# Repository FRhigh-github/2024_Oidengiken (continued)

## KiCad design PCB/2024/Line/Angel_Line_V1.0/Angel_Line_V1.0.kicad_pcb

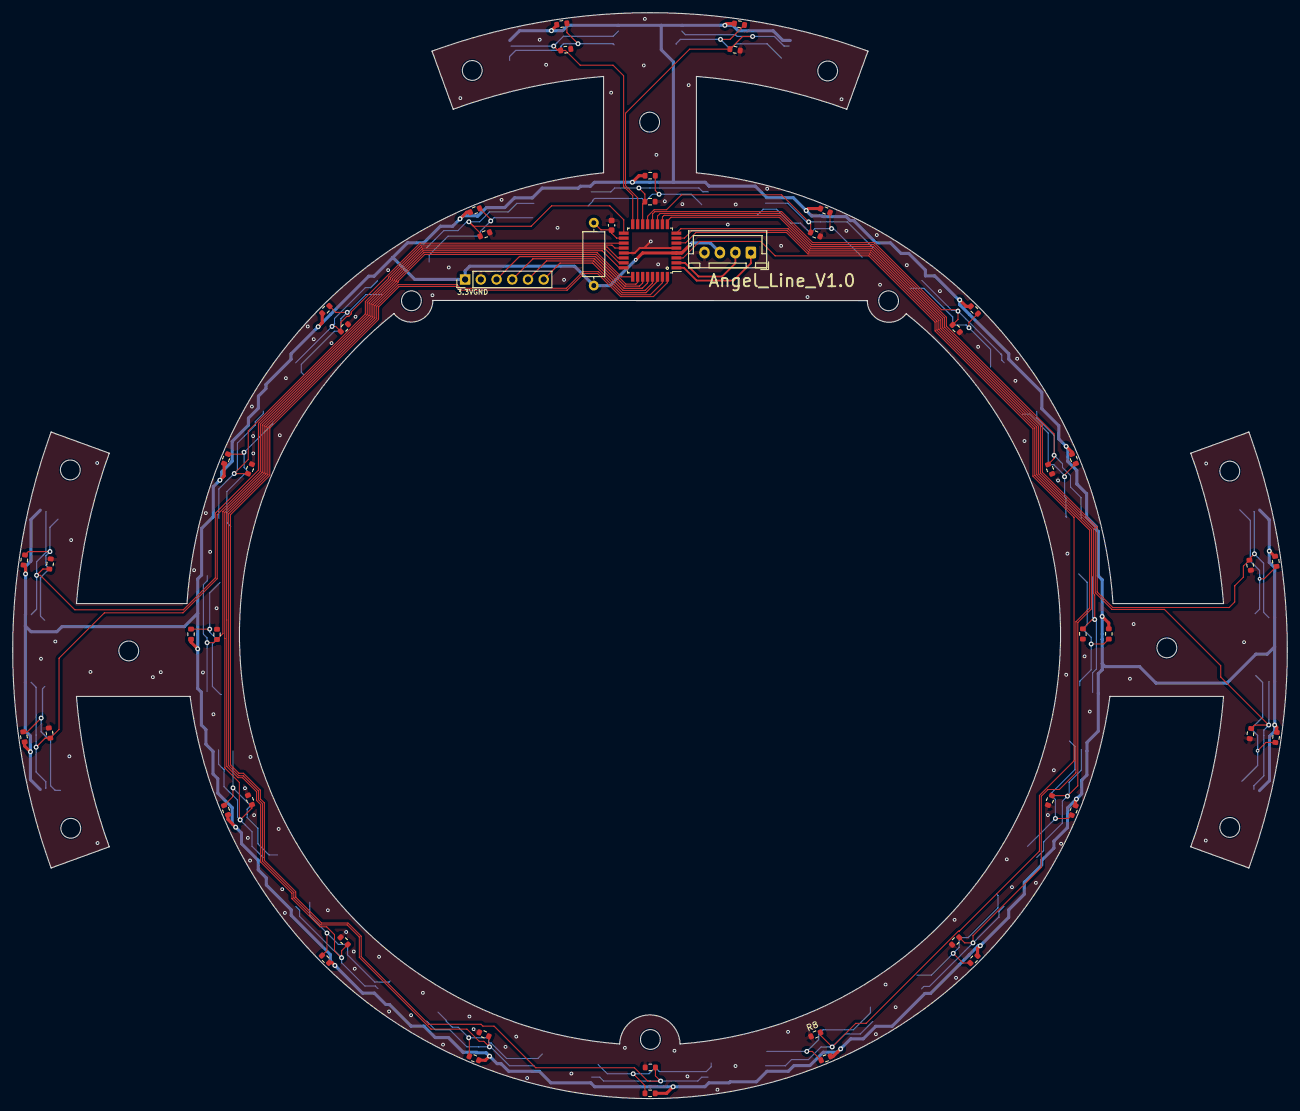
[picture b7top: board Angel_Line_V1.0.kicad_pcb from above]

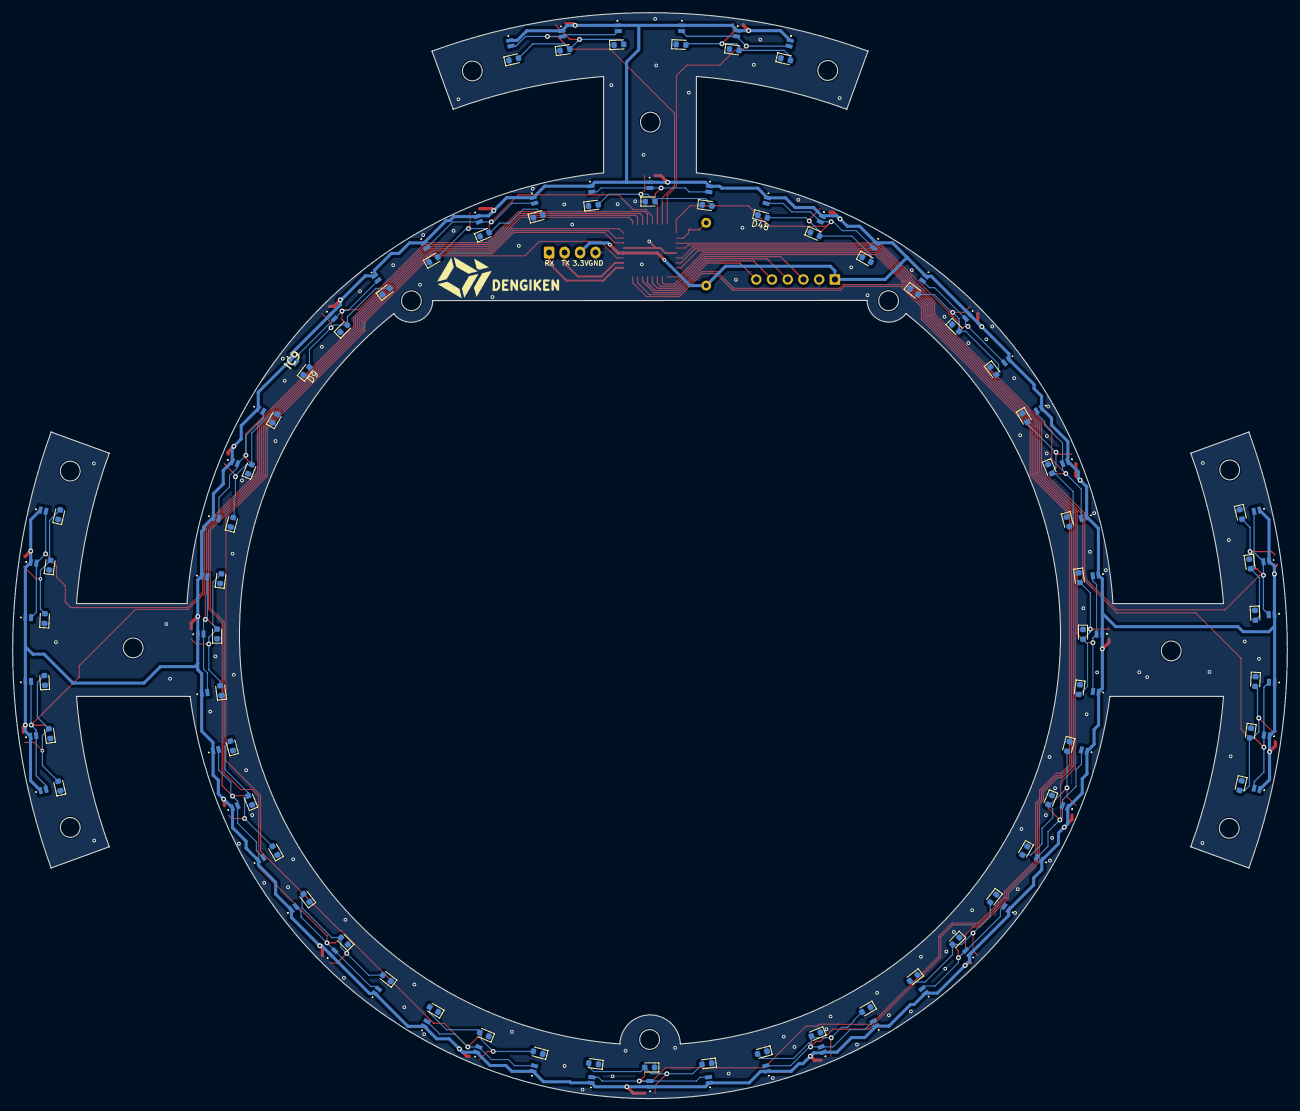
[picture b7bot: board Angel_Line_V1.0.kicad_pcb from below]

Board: 2 copper layers, 206.0 x 175.5 mm, 181 parts (132 on the bottom side), 53 nets.

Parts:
C1: C; C_0603_1608Metric
D1, D2, D3, D4, D5, D6, D7, D8, D9, D10, D11, D12, D13, D14, D15, D16, D17, D18, D19, D20, D21, D22, D23, D24, D25, D26, D27, D28, D29, D30, D31, D32, D33, D34, D35, D36, D37, D38, D39, D40, D41, D42, D43, D44, D45, D46, D47, D48, D49, D50, D51, D52, D53, D54, D55, D56, D57, D58, D59, D60, D61, D62, D63, D64, D65, D66: LED; LED_0603_1608Metric
IC1, IC2, IC3, IC4, IC5, IC6, IC7, IC8, IC9, IC10, IC11, IC12, IC13, IC14, IC15, IC16, IC17, IC18, IC19, IC20, IC21, IC22, IC23, IC24, IC25, IC26, IC27, IC28, IC29, IC30, IC31, IC32, IC33, IC34, IC35, IC36, IC37, IC38, IC39, IC40, IC41, IC42, IC43, IC44, IC45, IC46, IC47, IC48, IC49, IC50, IC51, IC52, IC53, IC54, IC55, IC56, IC57, IC58, IC59, IC60, IC67, IC68, IC69, IC70, IC71, IC72: NJL7502R
J1: Conn_01x06_Female; PinHeader_1x06_P2.54mm_Vertical
J2: Conn_01x04_Socket; JST_XH_B4B-XH-A_1x04_P2.50mm_Vertical
L1: L; L_Axial_L7.0mm_D3.3mm_P10.16mm_Horizontal_Fastron_MICC
R1, R2, R3, R4, R5, R6, R7, R8, R9, R10, R11, R12, R13, R14, R15, R16, R21, R22, R23, R24, R27, R28: 50k; R_0603_1608Metric
R17, R18, R19, R20, R25, R26, R29, R30, R31, R32, R33, R34, R35, R36, R37, R38, R39, R40, R41, R42, R43, R44: 100; R_0603_1608Metric
U1: ATtiny828-A; TQFP-32_7x7mm_P0.8mm

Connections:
A0: IC1.2 (E), IC2.2 (E), IC3.2 (E), R1.2, U1.14 (PA5)
A1: IC4.2 (E), IC5.2 (E), IC6.2 (E), R2.2, U1.13 (PA4)
A2: IC7.2 (E), IC8.2 (E), IC9.2 (E), R3.2, U1.12 (PA3)
A3: IC10.2 (E), IC11.2 (E), IC12.2 (E), R4.2, U1.11 (PA2)
A4: IC13.2 (E), IC14.2 (E), IC15.2 (E), R5.2, U1.8 (PC7)
A5: IC16.2 (E), IC17.2 (E), IC18.2 (E), R6.2, U1.7 (PC6)
A6: IC19.2 (E), IC20.2 (E), IC21.2 (E), R7.2, U1.6 (PC5)
A7: IC22.2 (E), IC23.2 (E), IC24.2 (E), R8.2, U1.3 (PC4)
A8: IC25.2 (E), IC26.2 (E), IC27.2 (E), R9.2, U1.32 (PC1)
A9: IC28.2 (E), IC29.2 (E), IC30.2 (E), R10.2, U1.31 (PC0)
A10: IC31.2 (E), IC32.2 (E), IC33.2 (E), R11.2, U1.26 (PB7)
A11: IC34.2 (E), IC35.2 (E), IC36.2 (E), R12.2, U1.25 (PB6)
A12: IC37.2 (E), IC38.2 (E), IC39.2 (E), R13.2, U1.24 (PB5)
A13: IC40.2 (E), IC41.2 (E), IC42.2 (E), R14.2, U1.20 (PB2)
A14: IC43.2 (E), IC44.2 (E), IC45.2 (E), R15.2, U1.19 (PB1)
A15: IC46.2 (E), IC47.2 (E), IC48.2 (E), R16.2, U1.17 (PB0)
A16: IC67.2 (E), IC68.2 (E), IC69.2 (E), R27.2, U1.16 (PA7)
A17: IC70.2 (E), IC71.2 (E), IC72.2 (E), R28.2, U1.15 (PA6)
A18: IC49.2 (E), IC50.2 (E), IC51.2 (E), R21.2, U1.10 (PA1)
A19: IC52.2 (E), IC53.2 (E), IC54.2 (E), R22.2, U1.9 (PA0)
A20: IC55.2 (E), IC56.2 (E), IC57.2 (E), R23.2, U1.23 (PB4)
A21: IC58.2 (E), IC59.2 (E), IC60.2 (E), R24.2, U1.22 (PB3)
Angel_RX: J2.1, U1.1 (PC2)
Angel_TX: J2.2, U1.2 (PC3)
MISO: J1.4, U1.28 (PD1)
MOSI: J1.3, U1.27 (PD0)
unnamed: D1.2 (A), D2.2 (A), D3.2 (A), R17.2
unnamed: D4.2 (A), D5.2 (A), D6.2 (A), R18.2
unnamed: D7.2 (A), D8.2 (A), D9.2 (A), R19.2
unnamed: D10.2 (A), D11.2 (A), D12.2 (A), R20.2
unnamed: D13.2 (A), D14.2 (A), D15.2 (A), R25.2
unnamed: D16.2 (A), D17.2 (A), D18.2 (A), R26.2
unnamed: D19.2 (A), D20.2 (A), D21.2 (A), R29.2
unnamed: D22.2 (A), D23.2 (A), D24.2 (A), R30.2
unnamed: D25.2 (A), D26.2 (A), D27.2 (A), R31.2
unnamed: D28.2 (A), D29.2 (A), D30.2 (A), R32.2
unnamed: D31.2 (A), D32.2 (A), D33.2 (A), R33.2
unnamed: D34.2 (A), D35.2 (A), D36.2 (A), R34.2
unnamed: D37.2 (A), D38.2 (A), D39.2 (A), R35.2
unnamed: D40.2 (A), D41.2 (A), D42.2 (A), R36.2
unnamed: D43.2 (A), D44.2 (A), D45.2 (A), R37.2
unnamed: D46.2 (A), D47.2 (A), D48.2 (A), R38.2
unnamed: D49.2 (A), D50.2 (A), D51.2 (A), R39.2
unnamed: D52.2 (A), D53.2 (A), D54.2 (A), R40.2
unnamed: D55.2 (A), D56.2 (A), D57.2 (A), R41.2
unnamed: D58.2 (A), D59.2 (A), D60.2 (A), R42.2
unnamed: D61.2 (A), D62.2 (A), D63.2 (A), R43.2
unnamed: D64.2 (A), D65.2 (A), D66.2 (A), R44.2
RESET: J1.5, U1.29 (PD2/~RESET)
SCL: J1.6, U1.30 (PD3)
VCC: IC1.1 (C), IC2.1 (C), IC3.1 (C), IC4.1 (C), IC5.1 (C), IC6.1 (C), IC7.1 (C), IC8.1 (C), IC9.1 (C), IC10.1 (C), IC11.1 (C), IC12.1 (C), IC13.1 (C), IC14.1 (C), IC15.1 (C), IC16.1 (C), IC17.1 (C), IC18.1 (C), IC19.1 (C), IC20.1 (C), IC21.1 (C), IC22.1 (C), IC23.1 (C), IC24.1 (C), IC25.1 (C), IC26.1 (C), IC27.1 (C), IC28.1 (C), IC29.1 (C), IC30.1 (C), IC31.1 (C), IC32.1 (C), IC33.1 (C), IC34.1 (C), IC35.1 (C), IC36.1 (C), IC37.1 (C), IC38.1 (C), IC39.1 (C), IC40.1 (C), IC41.1 (C), IC42.1 (C), IC43.1 (C), IC44.1 (C), IC45.1 (C), IC46.1 (C), IC47.1 (C), IC48.1 (C), IC49.1 (C), IC50.1 (C), IC51.1 (C), IC52.1 (C), IC53.1 (C), IC54.1 (C), IC55.1 (C), IC56.1 (C), IC57.1 (C), IC58.1 (C), IC59.1 (C), IC60.1 (C), IC67.1 (C), IC68.1 (C), IC69.1 (C), IC70.1 (C), IC71.1 (C), IC72.1 (C), J1.1, J2.3, L1.1, R17.1, R18.1, R19.1, R20.1, R25.1, R26.1, R29.1, R30.1, R31.1, R32.1, R33.1, R34.1, R35.1, R36.1, R37.1, R38.1, R39.1, R40.1, R41.1, R42.1, R43.1, R44.1, U1.4 (VCC)
VCCA: C1.1, L1.2, U1.18 (AVCC)
VSS: C1.2, D1.1 (K), D2.1 (K), D3.1 (K), D4.1 (K), D5.1 (K), D6.1 (K), D7.1 (K), D8.1 (K), D9.1 (K), D10.1 (K), D11.1 (K), D12.1 (K), D13.1 (K), D14.1 (K), D15.1 (K), D16.1 (K), D17.1 (K), D18.1 (K), D19.1 (K), D20.1 (K), D21.1 (K), D22.1 (K), D23.1 (K), D24.1 (K), D25.1 (K), D26.1 (K), D27.1 (K), D28.1 (K), D29.1 (K), D30.1 (K), D31.1 (K), D32.1 (K), D33.1 (K), D34.1 (K), D35.1 (K), D36.1 (K), D37.1 (K), D38.1 (K), D39.1 (K), D40.1 (K), D41.1 (K), D42.1 (K), D43.1 (K), D44.1 (K), D45.1 (K), D46.1 (K), D47.1 (K), D48.1 (K), D49.1 (K), D50.1 (K), D51.1 (K), D52.1 (K), D53.1 (K), D54.1 (K), D55.1 (K), D56.1 (K), D57.1 (K), D58.1 (K), D59.1 (K), D60.1 (K), D61.1 (K), D62.1 (K), D63.1 (K), D64.1 (K), D65.1 (K), D66.1 (K), J1.2, J2.4, R1.1, R2.1, R3.1, R4.1, R5.1, R6.1, R7.1, R8.1, R9.1, R10.1, R11.1, R12.1, R13.1, R14.1, R15.1, R16.1, R21.1, R22.1, R23.1, R24.1, R27.1, R28.1, U1.5 (GND), U1.21 (GND)

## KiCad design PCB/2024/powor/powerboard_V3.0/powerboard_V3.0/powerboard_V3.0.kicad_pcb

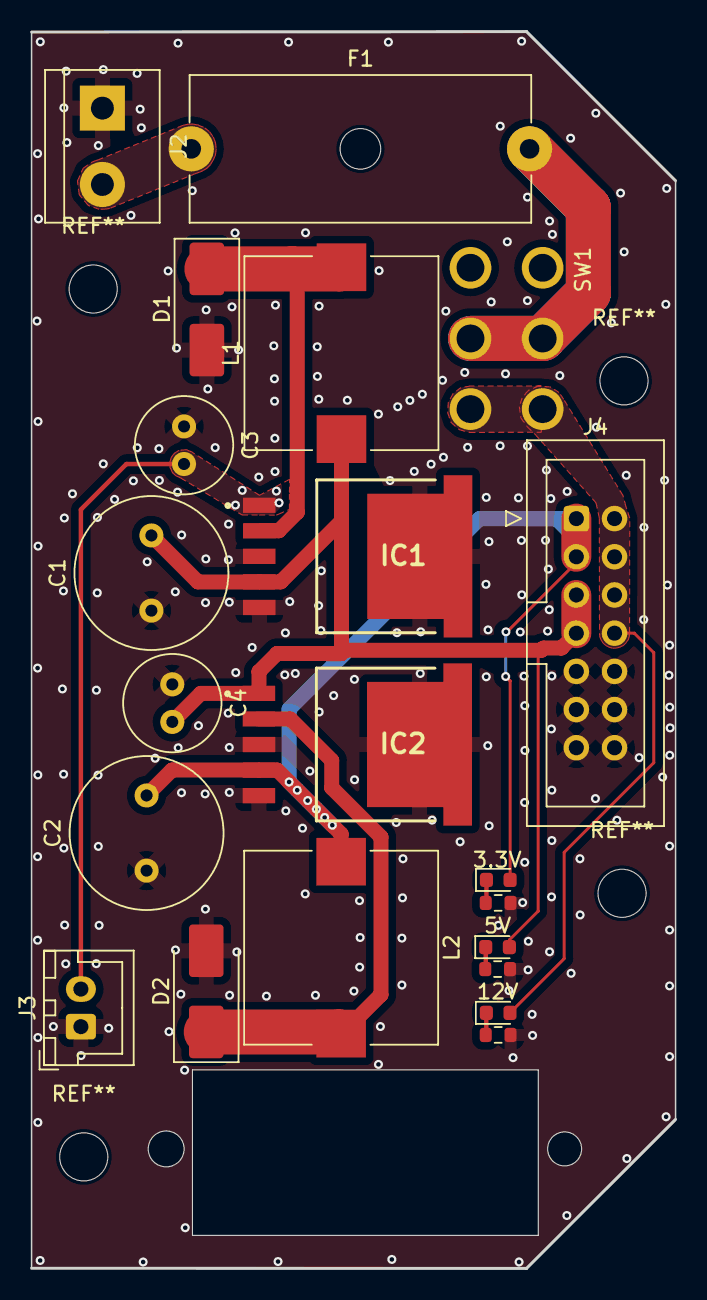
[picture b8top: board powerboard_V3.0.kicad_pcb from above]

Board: 2 copper layers, 42.8 x 82.3 mm, 21 parts (0 on the bottom side), 11 nets.

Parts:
3.3V, 5V, 12V: LED; LED_0603_1608Metric
C1, C2: 1000uF; C_Radial_D10.0mm_H12.5mm_P5.00mm
C3, C4: 100uF; C_Radial_D6.3mm_H7.0mm_P2.50mm
D1, D2: D; D_SMB_Handsoldering
F1: Fuse; Fuseholder_Cylinder-5x20mm_Schurter_0031_8201_Horizontal_Op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
IC1: LM2576SX-5.0_NOPB; KTT0005B
IC2: LM2576SX-3.3_NOPB; KTT0005B
J2: Conn_01x02_Female; TerminalBlock_bornier-2_P5.08mm
J3: 電圧計; JST_XH_B2B-XH-A_1x02_P2.50mm_Vertical
J4: Conn_02x07_Odd_Even; IDC-Header_2x07_P2.54mm_Vertical
L1, L2: 100uH; L_Vishay_IHLP-5050
R1, R2, R3: R; R_0603_1608Metric
SW1: SW_Push_DPDT; Toggle

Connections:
+3.3V: 3.3V.2 (A), C2.2, IC2.4 (FEEDBACK), J4.1, J4.3, L2.1
+5V: 5V.2 (A), C1.2, C4.2, IC1.4 (FEEDBACK), IC2.1 (VIN), J4.5, J4.7, L1.1
+12V: 12V.2 (A), C3.2, IC1.1 (VIN), J3.2, J4.2, J4.4, J4.6, J4.8, SW1.1 (A), SW1.4 (A)
GND: C1.1, C2.1, C3.1, C4.1, D1.2 (A), D2.2 (A), IC1.3 (GROUND), IC1.5 (~ON/OFF), IC1.6 (GND), IC2.3 (GROUND), IC2.5 (~ON/OFF), IC2.6 (GND), J2.1, J3.1, J4.9, J4.10, J4.11, J4.12, J4.13, J4.14, R1.1, R2.1, R3.1
unnamed: D1.1 (K), IC1.2 (OUTPUT), L1.2
unnamed: D2.1 (K), IC2.2 (OUTPUT), L2.2
unnamed: 5V.1 (K), R1.2
unnamed: 3.3V.1 (K), R2.2
unnamed: 12V.1 (K), R3.2
unnamed: F1.2, SW1.2 (B), SW1.5 (B)
unnamed: F1.1, J2.2

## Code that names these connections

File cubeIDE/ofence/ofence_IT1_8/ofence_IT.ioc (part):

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Mcu.Name=STM32F446R(C-E)Tx
Mcu.Package=LQFP64
Mcu.UserName=STM32F446RETx
PA0-WKUP.Mode=Asynchronous
PA0-WKUP.Signal=UART4_TX
PA1.Mode=Asynchronous
PA1.Signal=UART4_RX
PA10.Mode=Asynchronous
PA10.Signal=USART1_RX
PA13.GPIOParameters=GPIO_Label
PA13.GPIO_Label=TMS
PA13.Mode=Serial_Wire
PA13.Signal=SYS_JTMS-SWDIO
PA14.GPIOParameters=GPIO_Label
PA14.GPIO_Label=TCK
PA14.Mode=Serial_Wire
PA14.Signal=SYS_JTCK-SWCLK
PA2.GPIOParameters=GPIO_Label
PA2.GPIO_Label=USART_TX
PA2.Mode=Asynchronous
PA2.Signal=USART2_TX
PA3.GPIOParameters=GPIO_Label
PA3.GPIO_Label=USART_RX
PA3.Mode=Asynchronous
PA3.Signal=USART2_RX
PA5.GPIOParameters=GPIO_Label
PA5.GPIO_Label=LD2 [Green Led]
PA5.Signal=GPIO_Output
PA9.Mode=Asynchronous
PA9.Signal=USART1_TX
PB0.Signal=S_TIM3_CH3
PB1.Signal=S_TIM3_CH4
PB10.Signal=S_TIM2_CH3
PB2.Signal=S_TIM2_CH4
PB3.GPIOParameters=GPIO_Label
PB3.GPIO_Label=SWO
PB3.Signal=SYS_JTDO-SWO
PC0.GPIOParameters=GPIO_Label
PC0.GPIO_Label=ST_SW
PC0.Signal=GPXTI0
PC10.Mode=Asynchronous
PC10.Signal=USART3_TX
PC11.Mode=Asynchronous
PC11.Signal=USART3_RX
PC12.Mode=Asynchronous
PC12.Signal=UART5_TX
PC13.GPIOParameters=GPIO_Label,GPIO_ModeDefaultEXTI
PC13.GPIO_Label=B1 [Blue PushButton]
PC13.GPIO_ModeDefaultEXTI=GPIO_MODE_IT_FALLING
PC13.Signal=GPXTI13
PC14-OSC32_IN.Mode=LSE-External-Oscillator
PC14-OSC32_IN.Signal=RCC_OSC32_IN
PC15-OSC32_OUT.Mode=LSE-External-Oscillator
PC15-OSC32_OUT.Signal=RCC_OSC32_OUT
PD2.Mode=Asynchronous
PD2.Signal=UART5_RX
PH0-OSC_IN.Mode=HSE-External-Oscillator
PH0-OSC_IN.Signal=RCC_OSC_IN
PH1-OSC_OUT.Mode=HSE-External-Oscillator
PH1-OSC_OUT.Signal=RCC_OSC_OUT
RCC.HSE_VALUE=8000000
RCC.SYSCLKFreq_VALUE=84000000
RCC.SYSCLKSource=RCC_SYSCLKSOURCE_PLLCLK
board=NUCLEO-F446RE
boardIOC=true

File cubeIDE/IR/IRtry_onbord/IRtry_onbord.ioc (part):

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Mcu.Name=STM32L412RBTxP
Mcu.Package=LQFP64
Mcu.UserName=STM32L412RBTxP
PA13\ (JTMS/SWDIO).GPIOParameters=GPIO_Label
PA13\ (JTMS/SWDIO).GPIO_Label=TMS
PA13\ (JTMS/SWDIO).Mode=Serial_Wire
PA13\ (JTMS/SWDIO).Signal=SYS_JTMS-SWDIO
PA14\ (JTCK/SWCLK).GPIOParameters=GPIO_Label
PA14\ (JTCK/SWCLK).GPIO_Label=TCK
PA14\ (JTCK/SWCLK).Mode=Serial_Wire
PA14\ (JTCK/SWCLK).Signal=SYS_JTCK-SWCLK
PA2.GPIOParameters=GPIO_Speed,GPIO_PuPd,GPIO_Label
PA2.GPIO_Label=USART_TX
PA2.GPIO_PuPd=GPIO_NOPULL
PA2.GPIO_Speed=GPIO_SPEED_FREQ_VERY_HIGH
PA2.Mode=Asynchronous
PA2.Signal=USART2_TX
PA3.GPIOParameters=GPIO_Speed,GPIO_PuPd,GPIO_Label
PA3.GPIO_Label=USART_RX
PA3.GPIO_PuPd=GPIO_NOPULL
PA3.GPIO_Speed=GPIO_SPEED_FREQ_VERY_HIGH
PA3.Mode=Asynchronous
PA3.Signal=USART2_RX
PA4.GPIOParameters=GPIO_Label
PA4.GPIO_Label=SMPS_EN [ADP5301ACBZ_VEN]
PA4.Signal=GPIO_Output
PA5.GPIOParameters=GPIO_Speed,GPIO_PuPd,GPIO_Label,GPIO_ModeDefaultOutputPP
PA5.GPIO_Label=SMPS_V1
PA5.GPIO_ModeDefaultOutputPP=GPIO_MODE_OUTPUT_PP
PA5.GPIO_PuPd=GPIO_NOPULL
PA5.GPIO_Speed=GPIO_SPEED_FREQ_LOW
PA5.Signal=GPIO_Output
PA6.GPIOParameters=GPIO_PuPd,GPIO_Label
PA6.GPIO_Label=SMPS_PG [ADP5301ACBZ_OUTOK]
PA6.GPIO_PuPd=GPIO_PULLUP
PA6.Signal=GPIO_Input
PA7.GPIOParameters=GPIO_Label
PA7.GPIO_Label=SMPS_SW [TS3A44159PWR_IN1_2]
PA7.Signal=GPIO_Output
PA9.GPIOParameters=GPIO_Label
PA9.GPIO_Label=IR1
PA9.Signal=GPIO_Input
PB13.GPIOParameters=GPIO_Label
PB13.GPIO_Label=LD4 [green Led]
PB13.Signal=GPIO_Output
PB3\ (JTDO/TRACESWO).GPIOParameters=GPIO_Label
PB3\ (JTDO/TRACESWO).GPIO_Label=SWO
PB3\ (JTDO/TRACESWO).Signal=SYS_JTDO-SWO
PC13.GPIOParameters=GPIO_PuPd,GPIO_Label,GPIO_ModeDefaultEXTI
PC13.GPIO_Label=B1 [Blue PushButton]
PC13.GPIO_ModeDefaultEXTI=GPIO_MODE_IT_FALLING
PC13.GPIO_PuPd=GPIO_NOPULL
PC13.Signal=GPXTI13
PC14-OSC32_IN\ (PC14).Mode=LSE-External-Oscillator
PC14-OSC32_IN\ (PC14).Signal=RCC_OSC32_IN
PC15-OSC32_OUT\ (PC15).Mode=LSE-External-Oscillator
PC15-OSC32_OUT\ (PC15).Signal=RCC_OSC32_OUT
PH0-OSC_IN\ (PH0).GPIOParameters=GPIO_Label
PH0-OSC_IN\ (PH0).GPIO_Label=MCO
PH0-OSC_IN\ (PH0).Mode=HSE-External-Clock-Source
PH0-OSC_IN\ (PH0).Signal=RCC_OSC_IN
PH1-OSC_OUT\ (PH1).Signal=RCC_OSC_OUT
RCC.HSE_VALUE=8000000
RCC.SYSCLKFreq_VALUE=80000000
RCC.SYSCLKSource=RCC_SYSCLKSOURCE_PLLCLK
board=NUCLEO-L412RB-P
boardIOC=true

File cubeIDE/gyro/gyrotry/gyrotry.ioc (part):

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Mcu.Name=STM32F303K(6-8)Tx
Mcu.Package=LQFP32
Mcu.UserName=STM32F303K8Tx
PA10.Mode=Asynchronous
PA10.Signal=USART1_RX
PA13.GPIOParameters=GPIO_Label
PA13.GPIO_Label=SWDIO
PA13.Mode=Serial_Wire
PA13.Signal=SYS_JTMS-SWDIO
PA14.GPIOParameters=GPIO_Label
PA14.GPIO_Label=SWCLK
PA14.Mode=Serial_Wire
PA14.Signal=SYS_JTCK-SWCLK
PA15.GPIOParameters=GPIO_Label
PA15.GPIO_Label=VCP_RX
PA15.Mode=Asynchronous
PA15.Signal=USART2_RX
PA2.GPIOParameters=GPIO_Label
PA2.GPIO_Label=VCP_TX
PA2.Mode=Asynchronous
PA2.Signal=USART2_TX
PA9.Mode=Asynchronous
PA9.Signal=USART1_TX
PB6.Mode=I2C
PB6.Signal=I2C1_SCL
PB7.Mode=I2C
PB7.Signal=I2C1_SDA
PF0\ /\ OSC_IN.GPIOParameters=GPIO_Label
PF0\ /\ OSC_IN.GPIO_Label=MCO
PF0\ /\ OSC_IN.Mode=HSE-External-Clock-Source
PF0\ /\ OSC_IN.Signal=RCC_OSC_IN
RCC.HSEPLLFreq_Value=8000000
RCC.HSE_VALUE=8000000
RCC.SYSCLKFreq_VALUE=8000000
board=NUCLEO-F303K8
boardIOC=true

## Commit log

2024-01-17 ファイル整理
2024-01-17 ファイル整理２
2024-01-17 pulseIn自作(aruduino)
2024-01-18 bord上でdegitalread高速化+pluseIn
2024-01-18 １次機体でpluseIn
    反応しすぎかも
2024-01-20 1次機体自作パルスイン(動かない)
2024-01-20 自作パルスインうごいた！！(要改善)
2024-01-24 何もやってない
2024-01-24 library_gyro追加
2024-01-24 ofence割り込み
2024-01-28 ライブラリーなしでgyroありで動かなかったから
2024-02-10 IR修正
2024-02-10 IRなぜか曲がる
2024-02-11 割り込み(無理やり)
2024-02-11 test複数
2024-02-11 割り込み追加
2024-02-11 2024年のPCBファイル追加
